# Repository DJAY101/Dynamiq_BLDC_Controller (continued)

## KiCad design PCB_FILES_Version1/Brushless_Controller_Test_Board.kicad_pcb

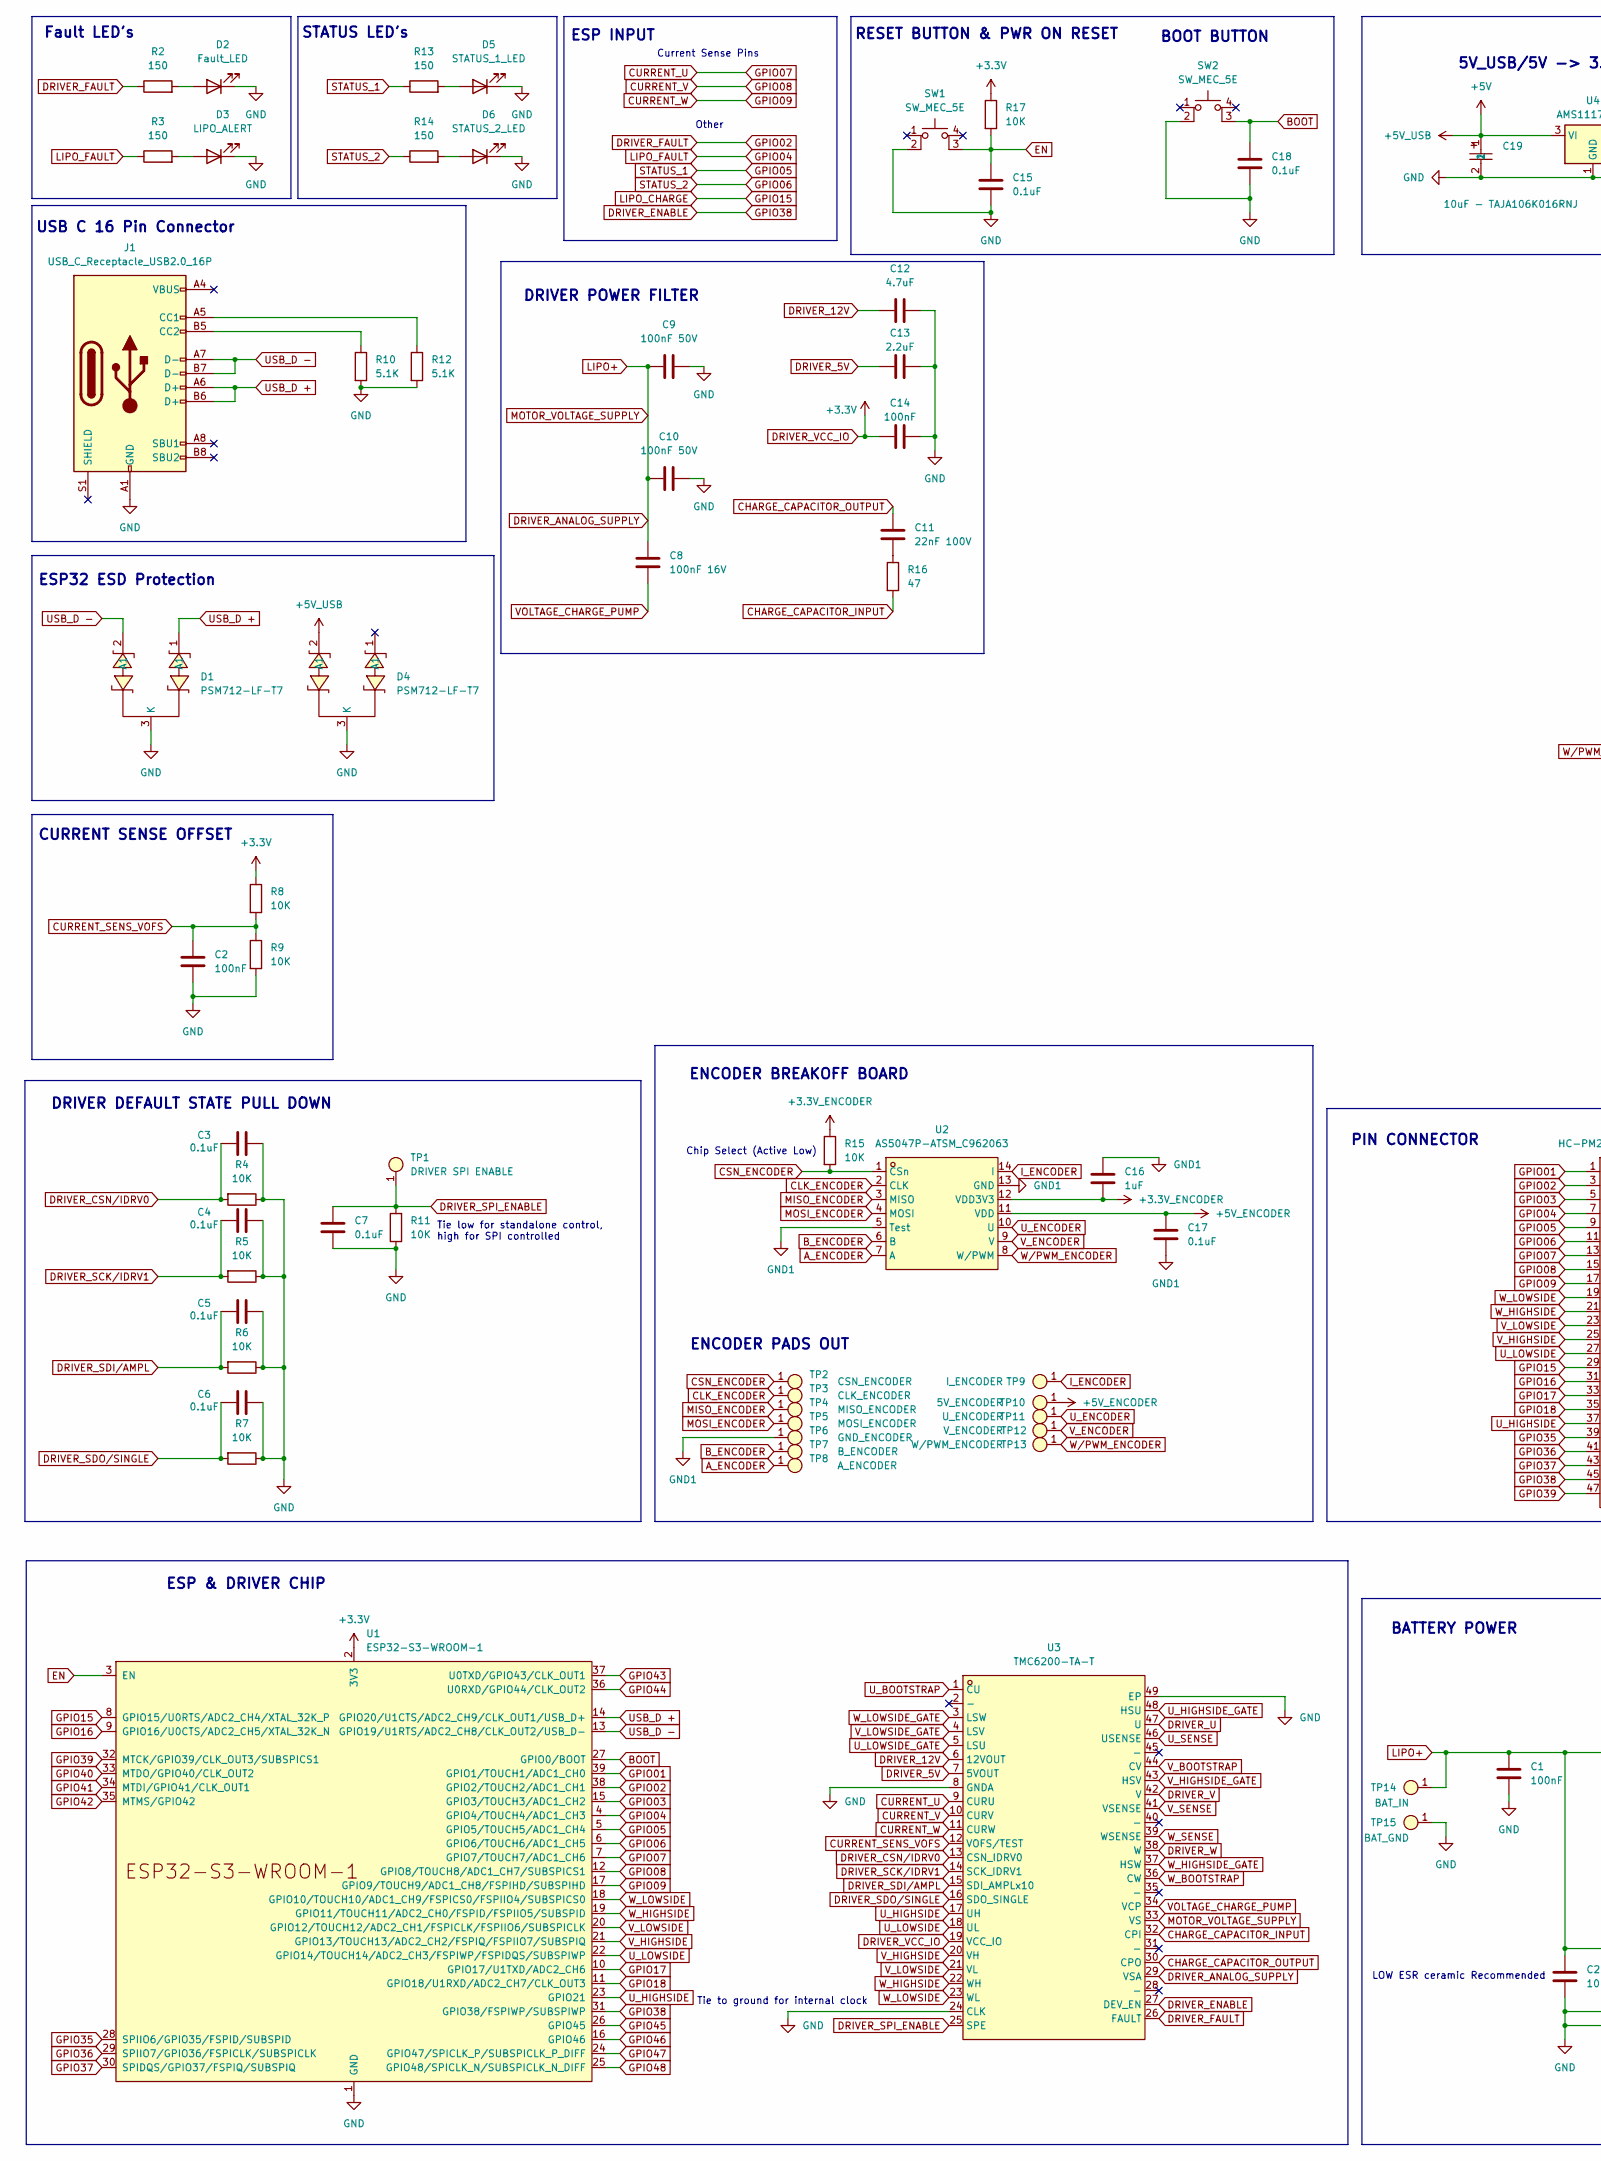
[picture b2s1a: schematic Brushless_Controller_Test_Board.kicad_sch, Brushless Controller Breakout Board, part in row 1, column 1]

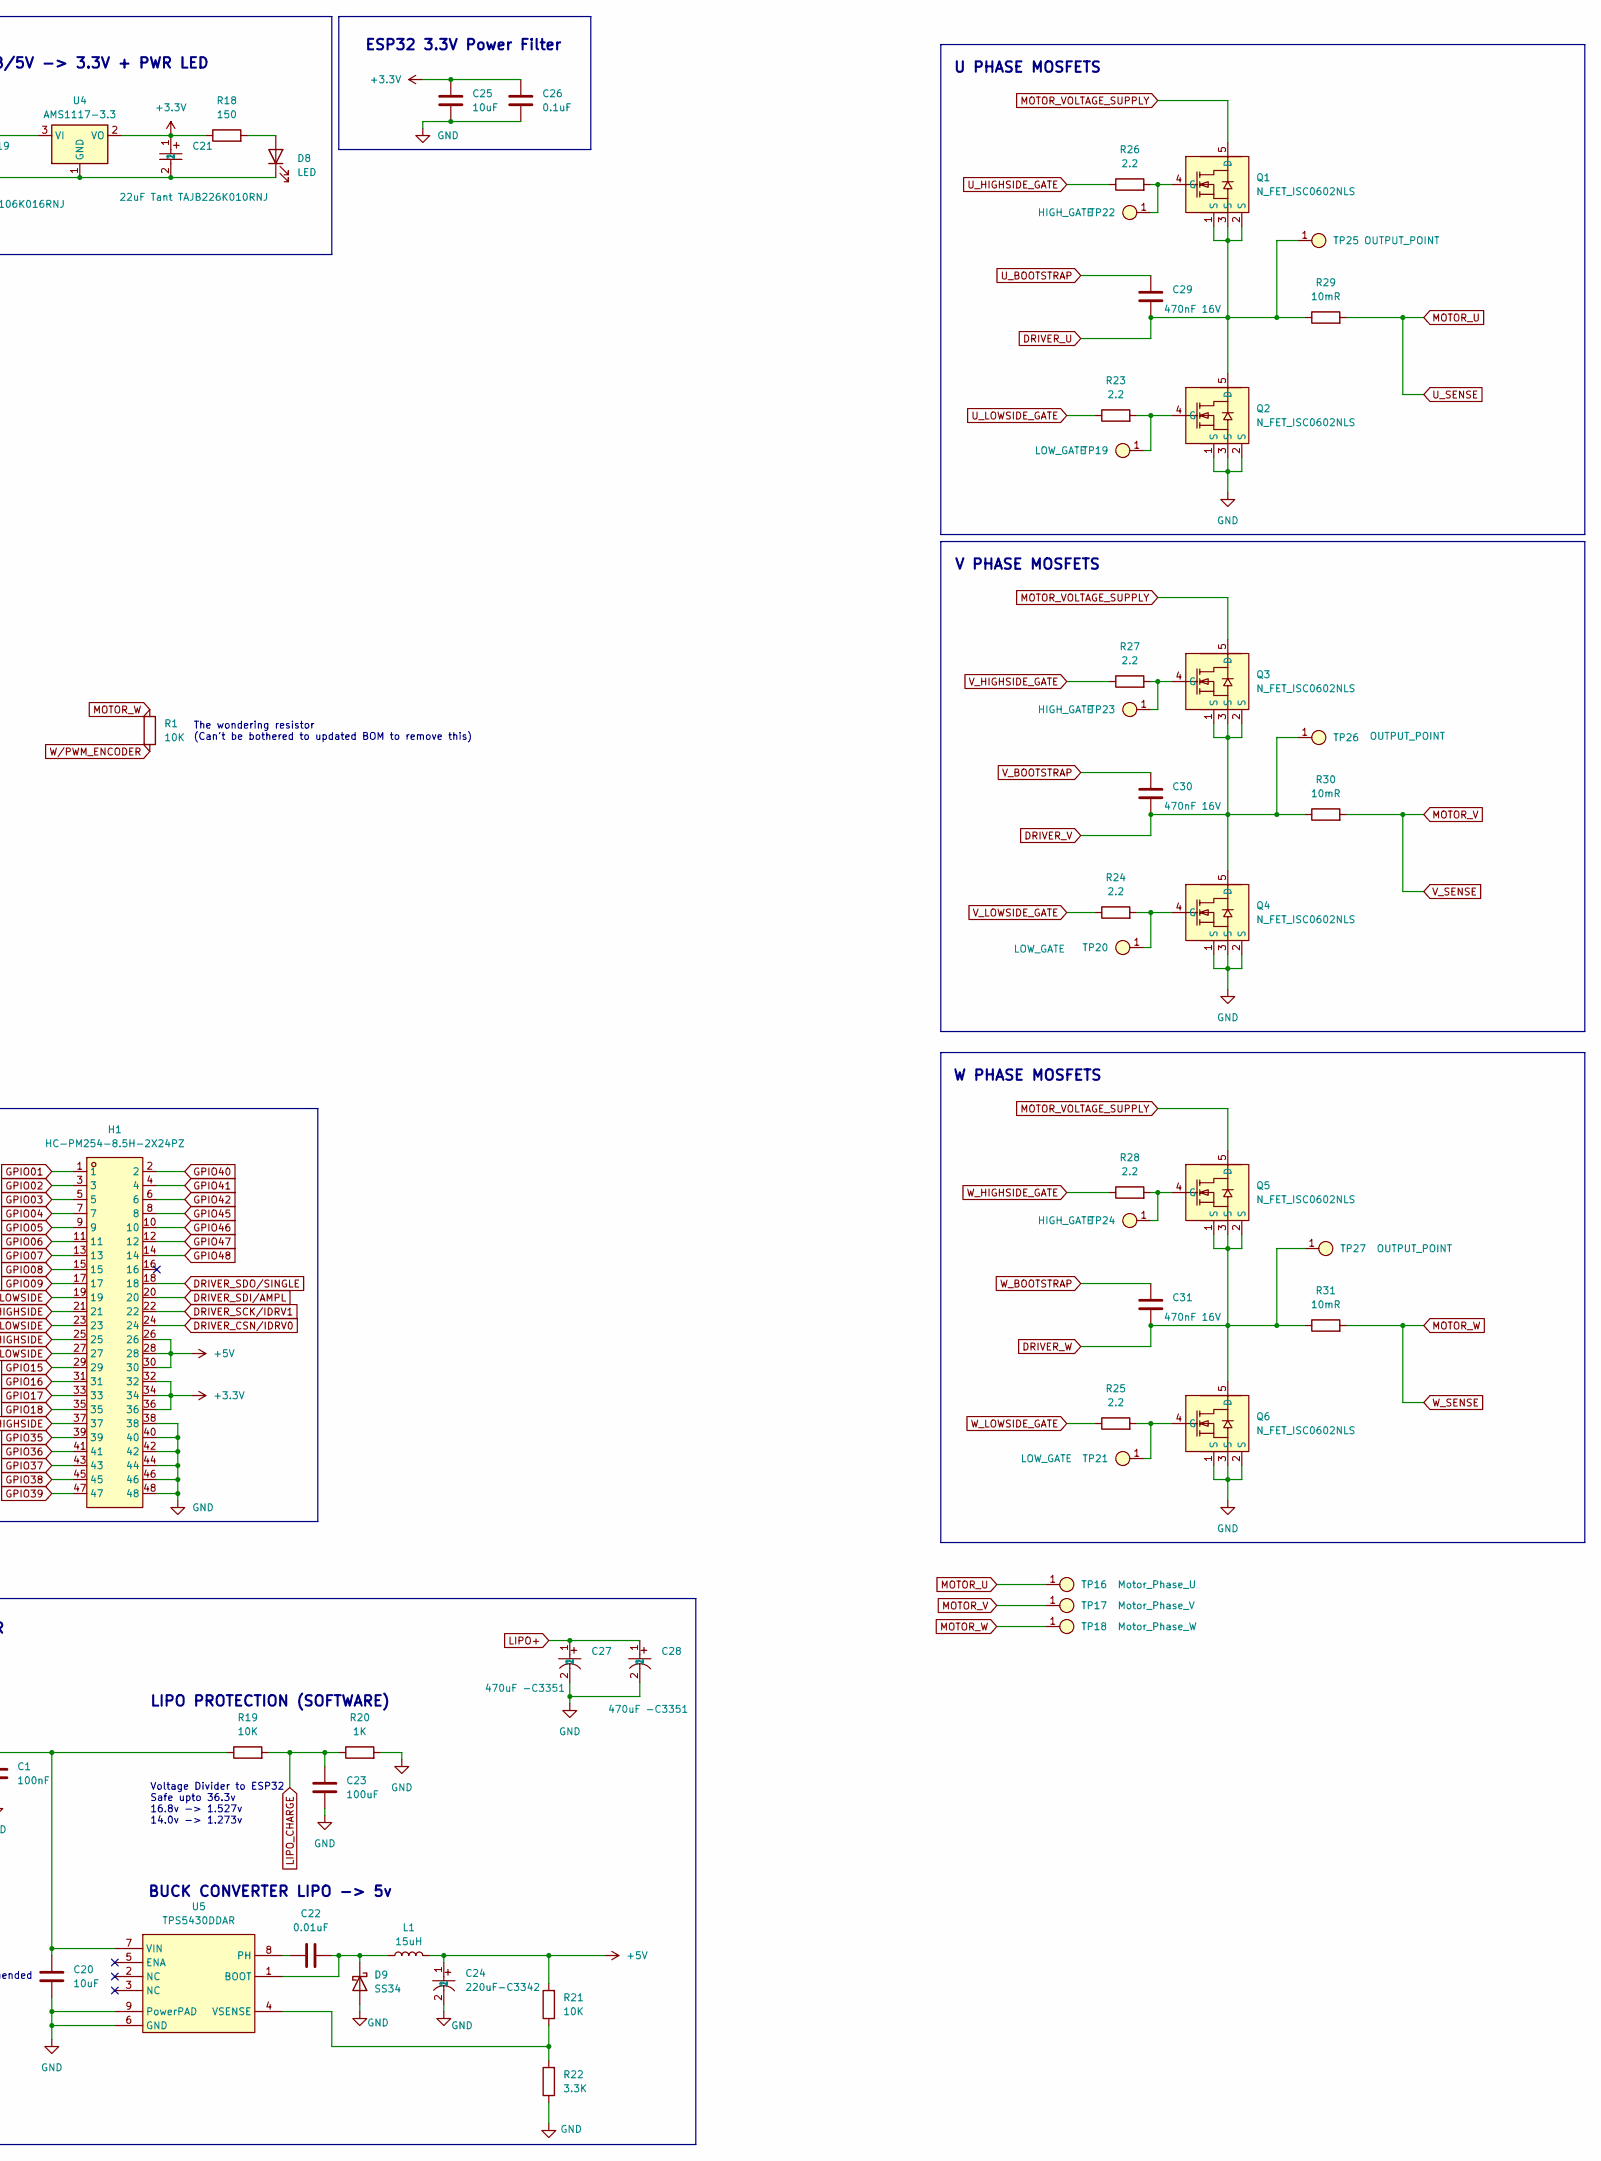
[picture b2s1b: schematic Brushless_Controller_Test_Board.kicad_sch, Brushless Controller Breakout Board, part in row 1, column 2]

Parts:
C1, C2, C14: 100nF; C_0805_2012Metric_Pad1.18x1.45mm_HandSolder
C3, C4, C5, C6, C7, C15, C17, C18, C26: 0.1uF; C_0805_2012Metric_Pad1.18x1.45mm_HandSolder
C8: 100nF 16V; C_01005_0402Metric_Pad0.57x0.30mm_HandSolder
C9, C10: 100nF 50V; C_1206_3216Metric_Pad1.33x1.80mm_HandSolder
C11: 22nF 100V; C_0805_2012Metric_Pad1.18x1.45mm_HandSolder
C12: 4.7uF; C_0805_2012Metric_Pad1.18x1.45mm_HandSolder
C13: 2.2uF; C_0805_2012Metric_Pad1.18x1.45mm_HandSolder
C16: 1uF; C_0805_2012Metric_Pad1.18x1.45mm_HandSolder
C19: 10uF - TAJA106K016RNJ; CAP-SMD_L3.2-W1.6-RD-C7171; LCSC Part C7171
C20, C25: 10uF; C_1206_3216Metric_Pad1.33x1.80mm_HandSolder
C21: 22uF Tant TAJB226K010RNJ; CAP-SMD_L3.5-W2.8-R-RD; LCSC Part C7198
C22: 0.01uF; C_0805_2012Metric_Pad1.18x1.45mm_HandSolder
C23: 100uF; C_1206_3216Metric_Pad1.33x1.80mm_HandSolder
C24: 220uF-C3342; CAP-SMD_BD6.3-L6.6-W6.6-FD; LCSC Part C3342
C27, C28: 470uF -C3351; CAP-SMD_BD10.0-L10.3-W10.3-LS11.3-FD; LCSC Part C3351
C29, C30, C31: 470nF 16V; C_0805_2012Metric_Pad1.18x1.45mm_HandSolder
D1, D4: PSM712-LF-T7; SOT-23-3_L3.0-W1.7-P0.95-LS2.9-BR; LCSC Part C32677
D2: Fault_LED; LED_0603_1608Metric_Pad1.05x0.95mm_HandSolder
D3: LIPO_ALERT; LED_0603_1608Metric_Pad1.05x0.95mm_HandSolder
D5: STATUS_1_LED; LED_0805_2012Metric_Pad1.15x1.40mm_HandSolder
D6: STATUS_2_LED; LED_0603_1608Metric_Pad1.05x0.95mm_HandSolder
D8: LED; LED_0805_2012Metric_Pad1.15x1.40mm_HandSolder
D9: SS34; SMA_L4.3-W2.6-LS5.2-RD
H1: HC-PM254-8.5H-2X24PZ; HDR-TH_48P-P2.54-V-F-R2-C24-S2.54; LCSC Part C27985239
J1: USB_C_Receptacle_USB2.0_16P; USB-C_SMD-TYPE-C-31-M-12
L1: 15uH; IND-SMD_L12.5-W12.5_RLF12545T
Q1, Q2, Q3, Q4, Q5, Q6: N_FET_ISC0602NLS; Infineon_PG-TDSON-8_6.15x5.15mm
R1, R4, R5, R6, R7, R8, R9, R11, R15, R17, R19, R21: 10K; R_0805_2012Metric_Pad1.20x1.40mm_HandSolder
R2, R3, R13, R14, R18: 150; R_0805_2012Metric_Pad1.20x1.40mm_HandSolder
R10, R12: 5.1K; R_0603_1608Metric_Pad0.98x0.95mm_HandSolder
R16: 47; R_0805_2012Metric_Pad1.20x1.40mm_HandSolder
R20: 1K; R_0805_2012Metric_Pad1.20x1.40mm_HandSolder
R22: 3.3K; R_0805_2012Metric_Pad1.20x1.40mm_HandSolder
R23, R24, R25, R26, R27, R28: 2.2; R_0805_2012Metric_Pad1.20x1.40mm_HandSolder
R29, R30, R31: 10mR; R_2512_6332Metric_Pad1.40x3.35mm_HandSolder
SW1, SW2: SW_MEC_5E; SW-SMD_4P-L5.2-W5.2-P3.70-LS6.5
TP1: DRIVER SPI ENABLE; PAD_TP
TP2: CSN_ENCODER; Small_Pad_4mm
TP3: CLK_ENCODER; Small_Pad_4mm
TP4: MISO_ENCODER; Small_Pad_4mm
TP5: MOSI_ENCODER; Small_Pad_4mm
TP6: GND_ENCODER; Small_Pad_4mm
TP7: B_ENCODER; Small_Pad_4mm
TP8: A_ENCODER; Small_Pad_4mm
TP9: I_ENCODER; Small_Pad_4mm
TP10: 5V_ENCODER; Small_Pad_4mm
TP11: U_ENCODER; Small_Pad_4mm
TP12: V_ENCODER; Small_Pad_4mm
TP13: W/PWM_ENCODER; Small_Pad_4mm
TP14: BAT_IN; Large_Pad_9mm
TP15: BAT_GND; Large_Pad_9mm
TP16: Motor_Phase_U; PWR_THRU_HOLE
TP17: Motor_Phase_V; PWR_THRU_HOLE
TP18: Motor_Phase_W; PWR_THRU_HOLE
TP19, TP20, TP21: LOW_GATE; PAD_TP
TP22, TP23, TP24: HIGH_GATE; PAD_TP
TP25, TP26, TP27: OUTPUT_POINT; PAD_TP
U1: ESP32-S3-WROOM-1
U2: AS5047P-ATSM_C962063; TSSOP-14_L5.0-W4.4-P0.65-LS6.4-BL; LCSC Part C962063
U3: TMC6200-TA-T; TQFP-48_L7.0-W7.0-P0.50-LS9.0-BL-EP; LCSC Part C465958
U4: AMS1117-3.3; SOT-223-3_TabPin2
U5: TPS5430DDAR; ESOP-8_L4.9-W3.9-P1.27-LS6.0-TL-EP; LCSC Part C9864

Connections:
+3.3V_ENCODER: C16.2, R15.1, U2.12 (VDD3V3)
+5V: C19.1, C24.1, D4.2 (A1), H1.26, H1.28, H1.30, L1.2, R21.2, U4.3 (VI)
+5V_ENCODER: C17.1, TP10.1, U2.11 (VDD)
A_ENCODER: TP8.1, U2.7 (A)
BOOT: C18.1, SW2.3 (K), U1.27 (GPIO0/BOOT)
B_ENCODER: TP7.1, U2.6 (B)
CHARGE_CAPACITOR_INPUT: R16.2, U3.32 (CPI)
CHARGE_CAPACITOR_OUTPUT: C11.2, U3.30 (CPO)
CLK_ENCODER: TP3.1, U2.2 (CLK)
CSN_ENCODER: R15.2, TP2.1, U2.1 (CSn)
CURRENT_SENS_VOFS: C2.1, R8.2, R9.1, U3.12 (VOFS/TEST)
CURRENT_U: H1.13, U1.7 (GPIO7/TOUCH7/ADC1_CH6), U3.9 (CURU)
CURRENT_V: H1.15, U1.12 (GPIO8/TOUCH8/ADC1_CH7/SUBSPICS1), U3.10 (CURV)
CURRENT_W: H1.17, U1.17 (GPIO9/TOUCH9/ADC1_CH8/FSPIHD/SUBSPIHD), U3.11 (CURW)
DRIVER_5V: C13.2, U3.7 (5VOUT)
DRIVER_12V: C12.2, U3.6 (12VOUT)
DRIVER_ANALOG_SUPPLY: C1.2, C8.1, C9.1, C10.1, C20.1, C27.1, C28.1, Q1.5 (D), Q3.5 (D), Q5.5 (D), R19.1, TP14.1, U3.29 (VSA), U3.33 (VS), U5.7 (VIN); also elsewhere on the board
DRIVER_CSN/IDRV0: C3.2, H1.24, R4.2, U3.13 (CSN_IDRV0)
DRIVER_ENABLE: H1.45, U1.31 (GPIO38/FSPIWP/SUBSPIWP), U3.27 (DEV_EN)
DRIVER_FAULT: H1.3, R2.1, U1.38 (GPIO2/TOUCH2/ADC1_CH1), U3.26 (FAULT)
DRIVER_SCK/IDRV1: C4.2, H1.22, R5.2, U3.14 (SCK_IDRV1)
DRIVER_SDI/AMPL: C5.2, H1.20, R6.2, U3.15 (SDI_AMPLx10)
DRIVER_SDO/SINGLE: C6.2, H1.18, R7.2, U3.16 (SDO_SINGLE)
DRIVER_SPI_ENABLE: C7.1, R11.2, TP1.1, U3.25 (SPE)
DRIVER_U: C29.2, Q1.1 (S), Q1.2 (S), Q1.3 (S), Q2.5 (D), R29.1, TP25.1, U3.47 (U)
DRIVER_V: C30.2, Q3.1 (S), Q3.2 (S), Q3.3 (S), Q4.5 (D), R30.1, TP26.1, U3.42 (V)
DRIVER_VCC_IO: C14.2, C21.1, C25.1, C26.1, H1.32, H1.34, H1.36, R8.1, R17.1, R18.1, U1.2 (3V3), U3.19 (VCC_IO), U4.2 (VO)
DRIVER_W: C31.2, Q5.1 (S), Q5.2 (S), Q5.3 (S), Q6.5 (D), R31.1, TP27.1, U3.38 (W)
EN: C15.1, R17.2, SW1.3 (K), U1.3 (EN)
GND: C1.1, C2.2, C3.1, C4.1, C5.1, C6.1, C7.2, C9.2, C10.2, C12.1, C13.1, C14.1, C15.2, C18.2, C19.2, C20.2, C21.2, C23.2, C24.2, C25.2, C26.2, C27.2, C28.2, D1.3 (K), D2.1 (K), D3.1 (K), D4.3 (K), D5.1 (K), D6.1 (K), D8.1 (K), D9.2 (A), H1.38, H1.40, H1.42, H1.44, H1.46, H1.48, J1.A1 (GND), J1.A12 (GND), J1.B1 (GND), J1.B12 (GND), Q2.1 (S), Q2.2 (S), Q2.3 (S), Q4.1 (S), Q4.2 (S), Q4.3 (S), Q6.1 (S), Q6.2 (S), Q6.3 (S), R4.1, R5.1, R6.1, R7.1, R9.2, R10.2, R11.1, R12.2, R20.2, R22.1, SW1.2, SW2.2, TP15.1, U1.1 (GND), U1.40 (GND), U1.41 (GND), U3.8 (GNDA), U3.24 (CLK), U3.49 (EP), U4.1 (GND), U5.6 (GND), U5.9 (PowerPAD); also elsewhere on the board
GND1: C16.1, C17.2, TP6.1, U2.5 (Test), U2.13 (GND)
GPIO01: H1.1, U1.39 (GPIO1/TOUCH1/ADC1_CH0)
GPIO03: H1.5, U1.15 (GPIO3/TOUCH3/ADC1_CH2)
GPIO04: H1.7, R3.1, U1.4 (GPIO4/TOUCH4/ADC1_CH3)
GPIO05: H1.9, R13.1, U1.5 (GPIO5/TOUCH5/ADC1_CH4)
GPIO06: H1.11, R14.1, U1.6 (GPIO6/TOUCH6/ADC1_CH5)
GPIO15: C23.1, H1.29, R19.2, R20.1, U1.8 (GPIO15/U0RTS/ADC2_CH4/XTAL_32K_P)
GPIO16: H1.31, U1.9 (GPIO16/U0CTS/ADC2_CH5/XTAL_32K_N)
GPIO17: H1.33, U1.10 (GPIO17/U1TXD/ADC2_CH6)
GPIO18: H1.35, U1.11 (GPIO18/U1RXD/ADC2_CH7/CLK_OUT3)
GPIO35: H1.39, U1.28 (SPIIO6/GPIO35/FSPID/SUBSPID)
GPIO36: H1.41, U1.29 (SPIIO7/GPIO36/FSPICLK/SUBSPICLK)
GPIO37: H1.43, U1.30 (SPIDQS/GPIO37/FSPIQ/SUBSPIQ)
GPIO39: H1.47, U1.32 (MTCK/GPIO39/CLK_OUT3/SUBSPICS1)
GPIO40: H1.2, U1.33 (MTDO/GPIO40/CLK_OUT2)
GPIO41: H1.4, U1.34 (MTDI/GPIO41/CLK_OUT1)
GPIO42: H1.6, U1.35 (MTMS/GPIO42)
GPIO43: U1.37 (U0TXD/GPIO43/CLK_OUT1)
GPIO44: U1.36 (U0RXD/GPIO44/CLK_OUT2)
GPIO45: H1.8, U1.26 (GPIO45)
GPIO46: H1.10, U1.16 (GPIO46)
GPIO47: H1.12, U1.24 (GPIO47/SPICLK_P/SUBSPICLK_P_DIFF)
GPIO48: H1.14, U1.25 (GPIO48/SPICLK_N/SUBSPICLK_N_DIFF)
I_ENCODER: TP9.1, U2.14 (I)
MISO_ENCODER: TP4.1, U2.3 (MISO)
MOSI_ENCODER: TP5.1, U2.4 (MOSI)
MOTOR_U: R29.2, TP16.1, U3.46 (USENSE); also elsewhere on the board
MOTOR_V: R30.2, TP17.1, U3.41 (VSENSE); also elsewhere on the board
MOTOR_W: R1.1, R31.2, TP18.1, U3.39 (WSENSE); also elsewhere on the board
unnamed: C11.1, R16.1
unnamed: D2.2 (A), R2.2
unnamed: D3.2 (A), R3.2
unnamed: D5.2 (A), R13.2
unnamed: D6.2 (A), R14.2
unnamed: D8.2 (A), R18.2
unnamed: C22.1, D9.1 (K), L1.1, U5.1 (BOOT)
unnamed: J1.A5 (CC1), R12.1
unnamed: J1.B5 (CC2), R10.1
unnamed: Q1.4 (G), R26.2, TP22.1
unnamed: Q2.4 (G), R23.2, TP19.1
unnamed: Q3.4 (G), R27.2, TP23.1
unnamed: Q4.4 (G), R24.2, TP20.1
unnamed: Q5.4 (G), R28.2, TP24.1
unnamed: Q6.4 (G), R25.2, TP21.1
unnamed: C22.2, U5.8 (PH)
unnamed: R21.1, R22.2, U5.4 (VSENSE)
USB_D +: D1.1 (A1), J1.A6 (D+), J1.B6 (D+), U1.14 (GPIO20/U1CTS/ADC2_CH9/CLK_OUT1/USB_D+)
USB_D -: D1.2 (A1), J1.A7 (D-), J1.B7 (D-), U1.13 (GPIO19/U1RTS/ADC2_CH8/CLK_OUT2/USB_D-)
U_BOOTSTRAP: C29.1, U3.1 (CU)
U_ENCODER: TP11.1, U2.10 (U)
U_HIGHSIDE: H1.37, U1.23 (GPIO21), U3.17 (UH)
U_HIGHSIDE_GATE: R26.1, U3.48 (HSU)
U_LOWSIDE: H1.27, U1.22 (GPIO14/TOUCH14/ADC2_CH3/FSPIWP/FSPIDQS/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), U3.18 (UL)
U_LOWSIDE_GATE: R23.1, U3.5 (LSU)
VOLTAGE_CHARGE_PUMP: C8.2, U3.34 (VCP)
V_BOOTSTRAP: C30.1, U3.44 (CV)
V_ENCODER: TP12.1, U2.9 (V)
V_HIGHSIDE: H1.25, U1.21 (GPIO13/TOUCH13/ADC2_CH2/FSPIQ/FSPIIO7/S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), U3.20 (VH)
V_HIGHSIDE_GATE: R27.1, U3.43 (HSV)
V_LOWSIDE: H1.23, U1.20 (GPIO12/TOUCH12/ADC2_CH1/FSPICLK/FSPIIO6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), U3.21 (VL)
V_LOWSIDE_GATE: R24.1, U3.4 (LSV)
W_BOOTSTRAP: C31.1, U3.36 (CW)
W_HIGHSIDE: H1.21, U1.19 (GPIO11/TOUCH11/ADC2_CH0/FSPID/FSPIIO5/S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), U3.22 (WH)
W_HIGHSIDE_GATE: R28.1, U3.37 (HSW)
W_LOWSIDE: H1.19, U1.18 (GPIO10/TOUCH10/ADC1_CH9/FSPICS0/FSPIIO4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), U3.23 (WL)
W_LOWSIDE_GATE: R25.1, U3.3 (LSW)
W/PWM_ENCODER: R1.2, TP13.1, U2.8 (W/PWM)

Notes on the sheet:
ESP32 3.3V Power Filter
Fault LED's
5V_USB/5V -> 3.3V + PWR LED
Other
U PHASE MOSFETS
ESP & DRIVER CHIP
Tie low for standalone control, high for SPI controlled
PIN CONNECTOR
Chip Select (Active Low)
ESP INPUT
RESET BUTTON & PWR ON RESET
DRIVER POWER FILTER
BOOT BUTTON
Current Sense Pins
CURRENT SENSE OFFSET
DRIVER DEFAULT STATE PULL DOWN
BATTERY POWER
The wondering resistor (Can't be bothered to updated BOM to remove this)
LIPO PROTECTION (SOFTWARE)
W PHASE MOSFETS
ENCODER PADS OUT
USB C 16 Pin Connector
Tie to ground for internal clock
Voltage Divider to ESP32 Safe upto 36.3v 16.8v -> 1.527v 14.0v -> 1.273v
ENCODER BREAKOFF BOARD
BUCK CONVERTER LIPO -> 5v
V PHASE MOSFETS
STATUS LED's
ESP32 ESD Protection
LOW ESR ceramic Recommended

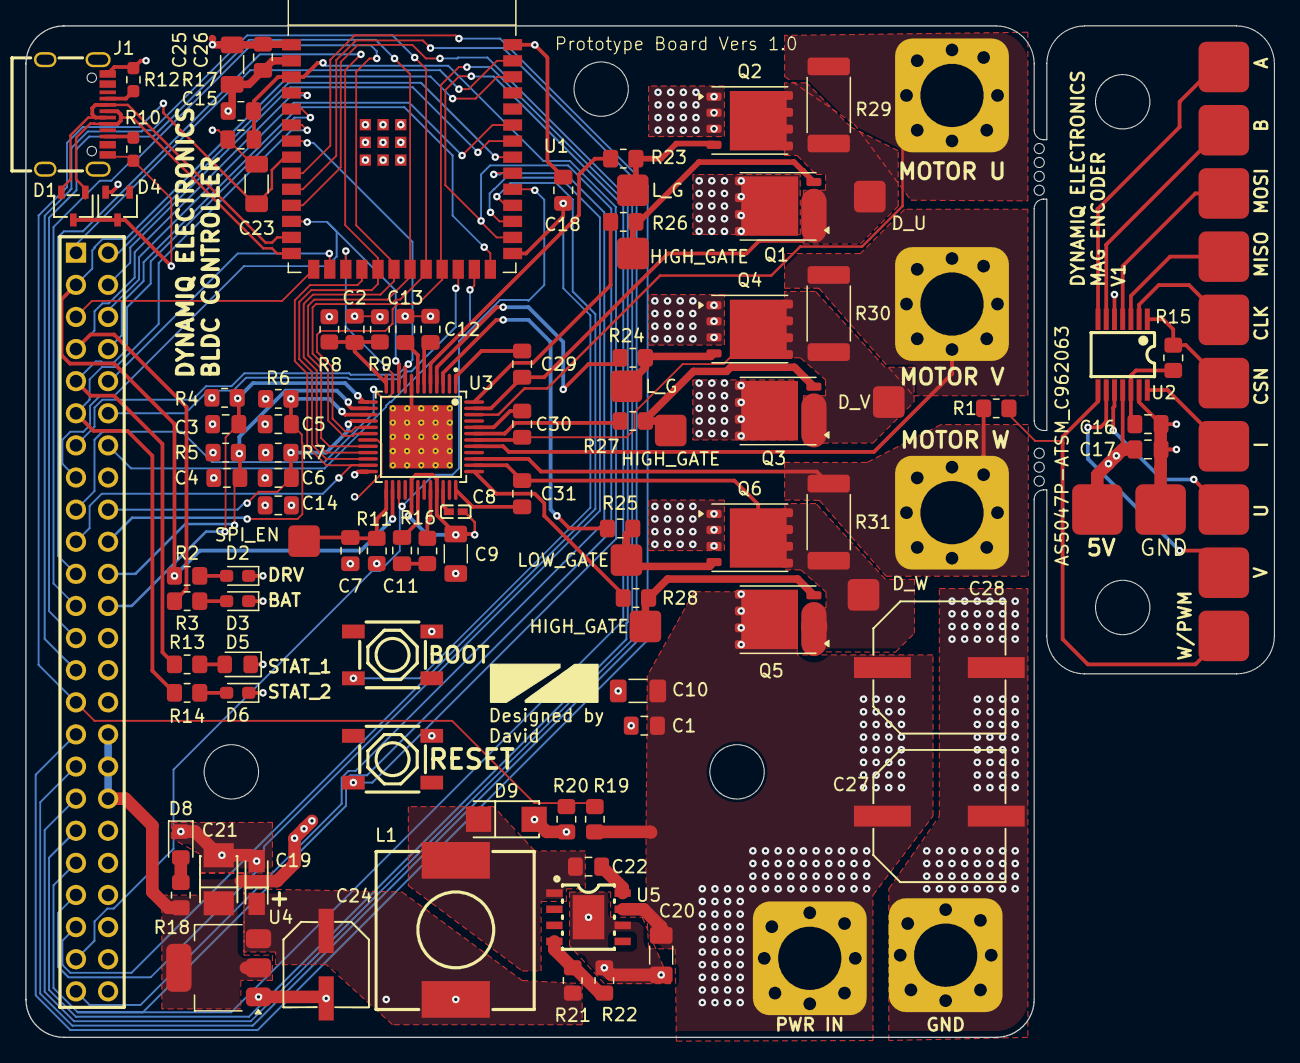
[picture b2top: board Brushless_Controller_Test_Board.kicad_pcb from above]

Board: 4 copper layers, 98.8 x 80.0 mm, 113 parts (0 on the bottom side), 95 nets.

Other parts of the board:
GND: BAT_GND; PWR_THRU_HOLE
MOTOR U: Motor_Phase_U; PWR_THRU_HOLE
MOTOR V: Motor_Phase_V; PWR_THRU_HOLE
MOTOR W: Motor_Phase_W; PWR_THRU_HOLE
PWR IN: BAT_IN; PWR_THRU_HOLE

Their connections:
DRIVER_ANALOG_SUPPLY: PWR IN.1; also elsewhere on the board
GND: GND.1; also elsewhere on the board
MOTOR_U: MOTOR U.1; also elsewhere on the board
MOTOR_V: MOTOR V.1; also elsewhere on the board
MOTOR_W: MOTOR W.1; also elsewhere on the board

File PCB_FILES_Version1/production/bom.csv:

Designator,Footprint,Quantity,Value,LCSC Part #
"C1, C14, C2",0805,3,100nF,
"C10, C9",1206,2,100nF 50V,
C11,0805,1,22nF 100V,
C12,0805,1,4.7uF,
C13,0805,1,2.2uF,
"C15, C17, C18, C26, C3, C4, C5, C6, C7",0805,9,0.1uF,
C16,0805,1,1uF,
C19,CAP-SMD_L3.2-W1.6-RD-C7171,1,10uF - TAJA106K016RNJ,C7171
"C20, C25",1206,2,10uF,
C21,CAP-SMD_L3.5-W2.8-R-RD,1,22uF Tant TAJB226K010RNJ,C7198
C22,0805,1,0.01uF,
C23,1206,1,100uF,
C24,CAP-SMD_BD6.3-L6.6-W6.6-FD,1,220uF-C3342,C3342
"C27, C28",CAP-SMD_BD10.0-L10.3-W10.3-LS11.3-FD,2,470uF -C3351,C3351
"C29, C30, C31",0805,3,470nF 16V,
C8,C0402,1,100nF 16V,
"D1, D4",SOT-23-3_L3.0-W1.7-P0.95-LS2.9-BR,2,PSM712-LF-T7,C32677
D2,0603,1,Fault_LED,
D3,0603,1,LIPO_ALERT,
D5,0805,1,STATUS_1_LED,
D6,0603,1,STATUS_2_LED,
D8,0805,1,LED,
D9,SMA_L4.3-W2.6-LS5.2-RD,1,SS34,
GND,PWR_THRU_HOLE,1,BAT_GND,
H1,HDR-TH_48P-P2.54-V-F-R2-C24-S2.54,1,HC-PM254-8.5H-2X24PZ,C27985239
J1,USB-C_SMD-TYPE-C-31-M-12,1,USB_C_Receptacle_USB2.0_16P,
L1,IND-SMD_L12.5-W12.5_RLF12545T,1,15uH,
MOTOR U,PWR_THRU_HOLE,1,Motor_Phase_U,
MOTOR V,PWR_THRU_HOLE,1,Motor_Phase_V,
MOTOR W,PWR_THRU_HOLE,1,Motor_Phase_W,
PWR IN,PWR_THRU_HOLE,1,BAT_IN,
"Q1, Q2, Q3, Q4, Q5, Q6",Infineon_PG-TDSON-8_6.15x5.15mm,6,N_FET_ISC0602NLS,
"R1, R11, R15, R17, R19, R21, R4, R5, R6, R7, R8, R9",0805,12,10K,
"R10, R12",0603,2,5.1K,
"R13, R14, R18, R2, R3",0805,5,150,
R16,0805,1,47,
R20,0805,1,1K,
R22,0805,1,3.3K,
"R23, R24, R25, R26, R27, R28",0805,6,2.2,
"R29, R30, R31",2512,3,10mR,
"SW1, SW2",SW-SMD_4P-L5.2-W5.2-P3.70-LS6.5,2,SW_MEC_5E,
TP1,PAD_TP,1,SPI_EN,
TP10,Small_Pad_4mm,1,5V_ENCODER,
TP11,Small_Pad_4mm,1,U_ENCODER,
TP12,Small_Pad_4mm,1,V_ENCODER,
TP13,Small_Pad_4mm,1,W/PWM_ENCODER,
"TP19, TP20",PAD_TP,2,L_G,
TP2,Small_Pad_4mm,1,CSN_ENCODER,
TP21,PAD_TP,1,LOW_GATE,
"TP22, TP23, TP24",PAD_TP,3,HIGH_GATE,
TP25,PAD_TP,1,D_U,
TP26,PAD_TP,1,D_V,
TP27,PAD_TP,1,D_W,
TP3,Small_Pad_4mm,1,CLK_ENCODER,
TP4,Small_Pad_4mm,1,MISO_ENCODER,
TP5,Small_Pad_4mm,1,MOSI_ENCODER,
TP6,Small_Pad_4mm,1,GND_ENCODER,
TP7,Small_Pad_4mm,1,B_ENCODER,
TP8,Small_Pad_4mm,1,A_ENCODER,
TP9,Small_Pad_4mm,1,I_ENCODER,
U1,ESP32-S3-WROOM-1,1,ESP32-S3-WROOM-1,
U2,TSSOP-14_L5.0-W4.4-P0.65-LS6.4-BL,1,AS5047P-ATSM_C962063,C962063
U3,TQFP-48_L7.0-W7.0-P0.50-LS9.0-BL-EP,1,TMC6200-TA-T,C465958
U4,SOT-223-3_TabPin2,1,AMS1117-3.3,
U5,ESOP-8_L4.9-W3.9-P1.27-LS6.0-TL-EP,1,TPS5430DDAR,C9864

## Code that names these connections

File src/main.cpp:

//////// Written by David J ////////
/////// ESP-32-S3 Wroom 1 Based BLDC Controller /////

/*
    The following program runs a simple brushless motor using sinusoidal control
    Copyright (C) 2025 Dawei Jin
    This program is free software: you can redistribute it and/or modify
    it under the terms of the GNU General Public License as published by
    the Free Software Foundation, either version 3 of the License, or
    any later version.

    This program is distributed in the hope that it will be useful,
    but WITHOUT ANY WARRANTY; without even the implied warranty of
    MERCHANTABILITY or FITNESS FOR A PARTICULAR PURPOSE.  See the
    GNU General Public License for more details.
*/

#include <stdlib.h>

#include "math.h"

#include "esp32-hal-ledc.h"
#include "esp32-hal-cpu.h"
#include "esp_attr.h"

// include custom classes
#include "../include/MotorController.h"
#include "../include/SerialManager.h"

// Include the library for the AS5047P sensor.
#include <AS5047P.h>

// ESP32 Freq
constexpr u_int32_t CPU_FREQ_MHZ {240};

// Mag Encoder SPI Bus Speed
constexpr u_int32_t AS5047P_CUSTOM_SPI_BUS_SPEED {1000000}; // 9Mhz
// Encoder SPI pins
constexpr u_int8_t ENCODER_CLK {39};
constexpr u_int8_t ENCODER_MISO {40};
constexpr u_int8_t ENCODER_MOSI {41};
constexpr u_int8_t ENCODER_CSN {42};

// The voltage at which the controller disables itself
constexpr double LIPO_DISABLE_VOLTAGE {14.0};

// initialize a new AS5047P sensor object.
AS5047P magEncoder(ENCODER_CSN, AS5047P_CUSTOM_SPI_BUS_SPEED);

// init my motor drivers and serial manager
MotorController* m_motorController = new MotorController();

SerialManager* m_serialManager = new SerialManager();

bool disableSerialInput = false;

//////////////////////////////////////////////////////////////////////////////////////////////////////
//////////////////////////////////////////////////////////////////////////////////////////////////////

// Map double values
double mapf(double x, double in_min, double in_max, double out_min, double out_max) {
  return (x - in_min) * (out_max - out_min) / (in_max - in_min) + out_min;
}


// Returns the current voltage of the lipo battery
double getLipoVoltage() {
  // Voltage offset of lipo due to voltage divider tolerance
  constexpr double LIPO_OFFSET = 0.7;
  return mapf(analogRead(LIPO_V_PIN), 0, 4095, 0, 36.3) + LIPO_OFFSET;
}

void executeSerialCommand(SerialManager* serialManager) {
   // Print out command recieved
  SerialCommand userCommand = serialManager->readSerialCommand();
  if (userCommand.cmd == ' ') return;

  Serial.print("Command: ");
  Serial.print(userCommand.cmd);
  Serial.print(" Set to: ");
  Serial.println(userCommand.value, 5);

  // Process the command here
  switch (userCommand.cmd) {
    case 'b':
        Serial.print("Battery at ");
        Serial.println(getLipoVoltage());
        break;
    case 'e':
        Serial.println("Driver Enabled");
        m_motorController->setDriverEnable(true);
        break;
    case 'd':
        Serial.println("Driver Disabled");
        m_motorController->setIdle();
        break;
    case 'p':
        Serial.print("Position set to: ");
        Serial.println(userCommand.value, 5);
        m_motorController->setClosedLoopPosition(userCommand.value);
        break;
    case 't':
         *m_motorController->getTestValue() = userCommand.value;
        break;
    case 'o':
        Serial.println("Percentage Output Mode Enabled");
        m_motorController->openLoopPercentageOutput(userCommand.value);
        break;
    case 'l':
        Serial.println("Percentage Output Mode Enabled");
        m_motorController->closedLoopPercentageOutput(userCommand.value);
        break;
    case 'z':
        Serial.println("Serial Input Disabled...");
        disableSerialInput = true;
        break;
    case 'c':
        m_motorController->calibrate();
        break;
    default: // optional
        Serial.println("No matching cmd");
  }
}

//////////////////////////////////////////////////////////////////////////////////////////////////////
//////////////////////////////////////////////////////////////////////////////////////////////////////

void setup() {
  // Set CPU Freq
  setCpuFrequencyMhz(CPU_FREQ_MHZ);
  
  // Setup Driver Pins for the motor controller
  m_motorController->init([]() {return magEncoder.readAngleDegree();});

  // Start serial communication
  m_serialManager->init();

  // Get the ESP32 to set the correct pins for encoder SPI (using its built in MUX)
  SPI.begin(ENCODER_CLK, ENCODER_MISO, ENCODER_MOSI, ENCODER_CSN);

  // Initialise the magnetic encoder
  while (!magEncoder.initSPI()) {
    Serial.println(F("Can't connect to the AS5047P sensor! Please check the connection..."));
    delay(5000);
  }
  delay(300);
}


bool lipoThresholdHit = false;
void loop() {


  double encoderAngle = magEncoder.readAngleDegree();
  
  m_motorController->update(magEncoder.readMagnitude());
  

  if (!disableSerialInput) {
    m_serialManager->updateSerialInput();
  }
  executeSerialCommand(m_serialManager);

  // Lipo protection if statement
  if (getLipoVoltage() < LIPO_DISABLE_VOLTAGE || lipoThresholdHit) {
    lipoThresholdHit = true;
    digitalWrite(LIPO_LED_PIN, HIGH);
    m_motorController->setDriverEnable(false);
    m_motorController->setIdle();
    Serial.println("Lipo Voltage Threshold hit");
  }
}

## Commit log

2025-07-20 Fixed ordering, code should now build
2025-07-20 Build Fixes & Created classes for motor controller
2025-07-21 Open loop control working code
    Moved everything into classes to cleanup the code.
    Open loop percentage output now works
    open loop position control now works
2025-07-21 closed loop control successfully integrated
2025-07-22 Using teleplot and changed encoder speed
2025-07-24 PCB Files uploaded
2025-07-24 Added GNU License
2025-07-24 Added things to readme
2025-07-31 Most of the schematic is completed
2025-08-02 Added pins
2025-08-05 Added soft starter to PCB
2025-08-09 Added ESD protection and test pins
2025-08-10 began part placement
2025-08-11 Completed Placement of Parts
2025-08-12 began working on the routing
2025-08-13 worked on traces
2025-08-14 Routing Complete
2025-08-14 Added silkscreen texts and logo
2025-08-19 Minor changes
2025-09-22 Edited code to work on board 1.1
2025-09-25 FOC current testing
2025-09-28 Debugging and Testing
2025-09-28 Added current reading function
2025-09-28 Cleaned up code
2025-09-29 Added logic to blink lights depending on operation
2025-09-29 Added calibration function
